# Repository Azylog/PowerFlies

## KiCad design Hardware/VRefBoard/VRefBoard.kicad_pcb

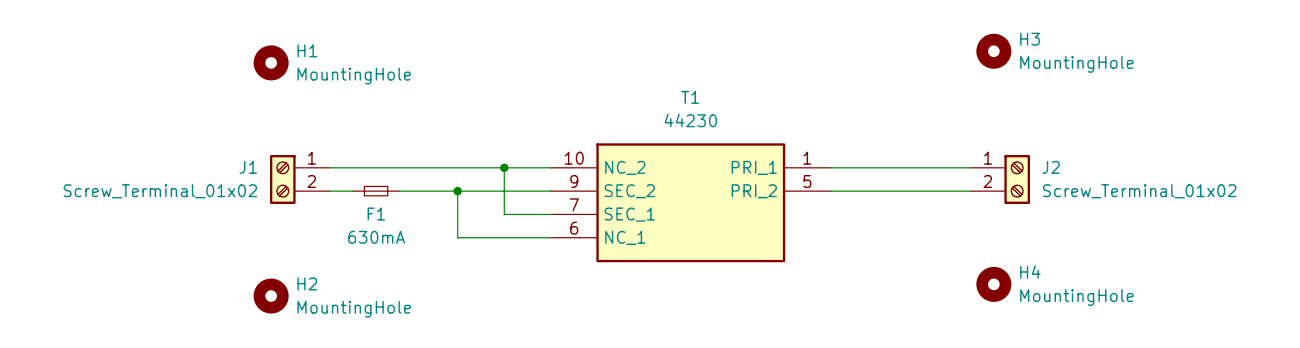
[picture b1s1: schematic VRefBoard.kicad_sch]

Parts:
F1: 630mA; 0PTF0078P
H1, H2, H3, H4: MountingHole; MountingHole_2.5mm
J1, J2: Screw_Terminal_01x02; TerminalBlock_Phoenix_MKDS-1,5-2-5.08_1x02_P5.08mm_Horizont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
T1: 44230; Manufacturer_Part_Number 44230

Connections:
unnamed: J1.1, T1.7 (SEC_1), T1.10 (NC_2)
unnamed: F1.1, J1.2
unnamed: J2.1, T1.1 (PRI_1)
unnamed: J2.2, T1.5 (PRI_2)
unnamed: F1.2, T1.6 (NC_1), T1.9 (SEC_2)

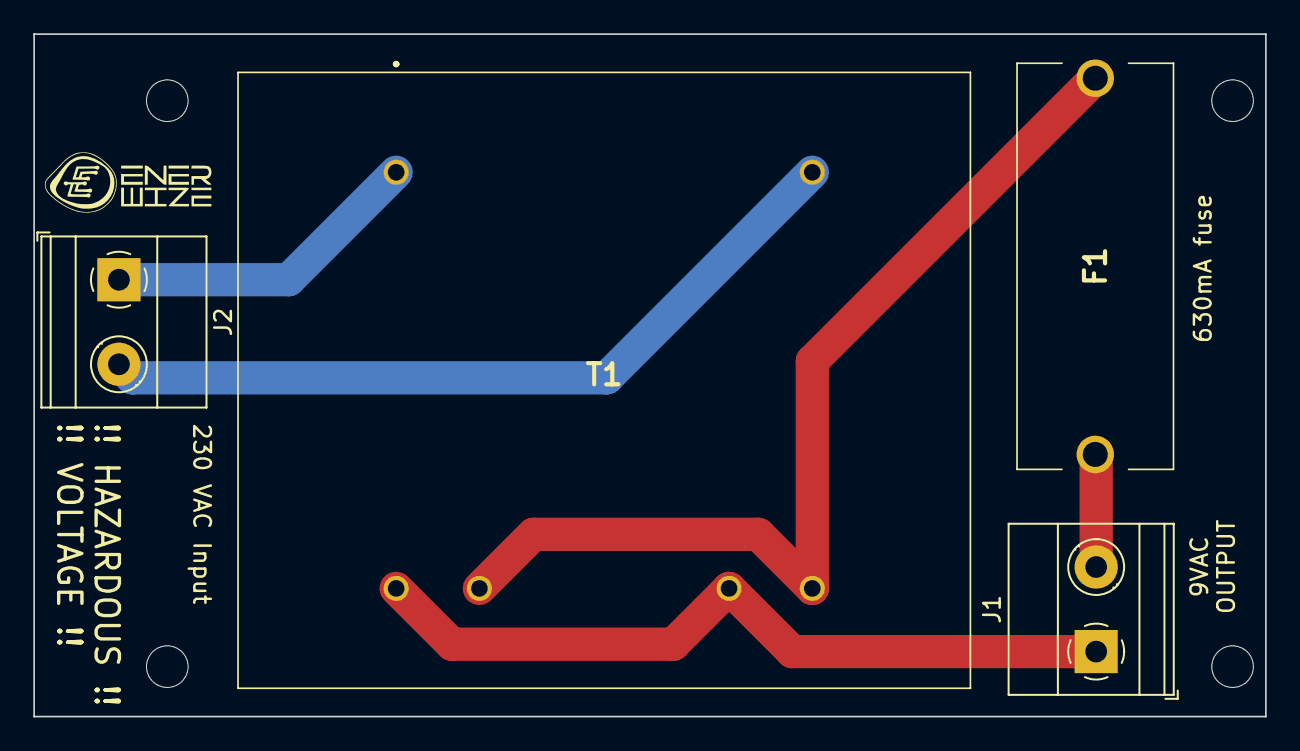
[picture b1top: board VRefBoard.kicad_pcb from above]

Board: 2 copper layers, 74.0 x 41.0 mm, 8 parts (0 on the bottom side), 5 nets.

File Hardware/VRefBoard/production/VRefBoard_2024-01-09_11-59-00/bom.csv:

Designator,Footprint,Quantity,Value,LCSC Part #
F1,0PTF0078P,1,630mA,
"H1, H2, H3, H4",MountingHole_2.5mm,4,MountingHole,
"J1, J2","TerminalBlock_Phoenix_MKDS-1,5-2-5.08_1x02_P5.08mm_Horizontal",2,Screw_Terminal_01x02,
T1,44230,1,44230,

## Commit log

2023-12-18 Add Esphome initial config files
2023-12-18 Readme file for v1.1
2023-12-18 Added Improv BLE Added workflows
2023-12-18 Moved workflow to correct locations
2023-12-18 Workflow testing
2023-12-18 Add frequency to all configs
2023-12-18 Workflow fix
2023-12-18 Removed empty lines
2023-12-18 Add workflow_call to publish
2023-12-18 Workflow test
2023-12-18 Added static files for publish workflow
2023-12-18 Fix workflow call
2023-12-18 Removed empty line
2023-12-18 Fix workflow_dispatch to run manually
2023-12-18 Initial gh-pages commit
2023-12-18 Deploying to gh-pages from @ Enerwize/PowerFlies@322073cf4c82ab84e5eb115ac9190304a85098ed 🚀
2023-12-19 Changes in wifi mode Remove improv over wifi
2023-12-19 Change to default output power
2023-12-21 Add dummy SSID in wifi to remove compile error
2023-12-21 Deploying to gh-pages from @ Enerwize/PowerFlies@dac8c752ae1547f102c5cf38cebc9e5c47d91ad7 🚀
2023-12-21 Roll back over previous commit
2023-12-21 Deploying to gh-pages from @ Enerwize/PowerFlies@7b97fb8a8bb4cecd88d4449fbd1e5a5e5906d8d8 🚀
2024-02-01 Initial commit for the Hardware directory (WIP) Initial commit of EmonESP version of software
2024-02-02 Added Home Assistant auto discovery for MQTT Some branding Moved config from EEPROM to Preference Made client name consistent for MQTT, DHCP and mDNS
2024-02-06 Add wifi-only config reset Some MQTT defaults (topic & server for H.A.) Fix broken OTA
2024-02-06 Bump 1.11
2024-08-13 Update device_base.yaml for new OTA platform
2024-08-13 Deploying to gh-pages from @ Enerwize/PowerFlies@abb4a20d03f0e05829f8280b4f240e7725d7a247 🚀
